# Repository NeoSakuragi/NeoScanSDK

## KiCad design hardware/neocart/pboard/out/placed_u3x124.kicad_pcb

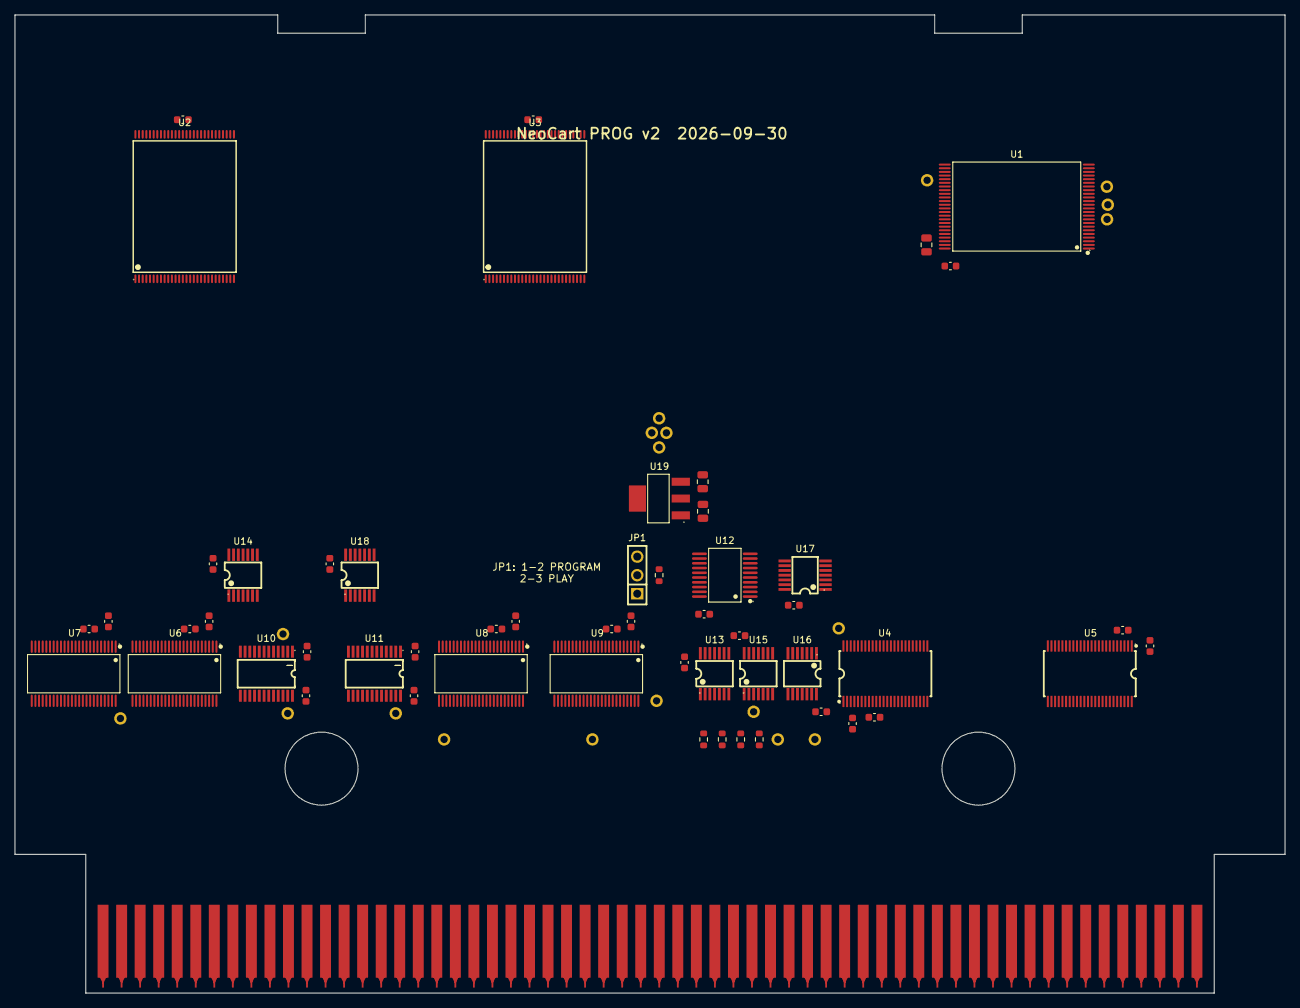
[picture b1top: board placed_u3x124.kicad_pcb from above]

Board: 2 copper layers, 174.0 x 134.0 mm, 75 parts (1 on the bottom side), 206 nets, no tracks yet.

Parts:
C1, C2, C3: 10u; C_0805_2012Metric
C4, C5, C6, C7, C8, C9, C10, C11, C12, C13, C14, C15, C16, C17, C18, C19, C20, C21, C22, C23, C24, C25, C26, C27, C28, C29: 100n; C_0603_1608Metric
J1: NeoGeo MVS Prog B Side Edge; neogeo-mvs-prog-b-side-edge
J2: NeoGeo MVS Prog A Side Edge; neogeo-mvs-prog-a-side-edge
JP1: MODE; HDR-TH_03P-P2.54-V-M
R1, R2, R3, R4, R5: 10k; R_0603_1608Metric
TP1, TP2: GND; TP_PTH_1.0
TP3: P3V3; TP_PTH_1.0
TP4: VCC5; TP_PTH_1.0
TP5: nPROG; TP_PTH_1.0
TP6: VDIR; TP_PTH_1.0
TP7: nP_OE; TP_PTH_1.0
TP8: nXCVR_EN; TP_PTH_1.0
TP9: FA19; TP_PTH_1.0
TP10: FA20; TP_PTH_1.0
TP11: FA21; TP_PTH_1.0
TP12: nVA_BUFOE; TP_PTH_1.0
TP13: nVB_BUFOE; TP_PTH_1.0
TP14: nRMPX; TP_PTH_1.0
TP15: nPMPX; TP_PTH_1.0
TP16: nAS; TP_PTH_1.0
TP17: CLK68K; TP_PTH_1.0
TP18: CLK4M; TP_PTH_1.0
TP19: nSLOTCS; TP_PTH_1.0
U1: S29GL064N; TSOP-48_L12.0-W18.4-P0.50-LS20.0-BL
U2, U3: S29GL128P; TSOP-56_L18.4-W14.0-P0.50-LS20.0-TL
U4, U5: SN74LVC16245A; TSSOP-48_L12.5-W6.1-P0.50-LS8.1-BL
U6, U7, U8, U9: 74LVC16374A; TSSOP-48_L12.6-W6.2-P0.50-LS8.1-BL
U10, U11: 74LVC8T245; TSSOP-24_L7.8-W4.4-P0.65-LS6.4-BL
U12: SN74AHC273; SSOP-20_L7.5-W5.2-P0.65-LS8.0-BL
U13, U14: SN74LVC08A; TSSOP-14_L5.0-W4.4-P0.65-LS6.4-BL
U15, U16, U17: 74LVC32A; TSSOP-14_L5.0-W4.4-P0.65-LS6.4-BL
U18: SN74LVC04A; TSSOP-14_L5.0-W4.4-P0.65-LS6.4-BL
U19: AMS1117-3.3; SOT-223-3_L6.5-W3.4-P2.30-LS7.0-BR

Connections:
A1: J1.5 (A1), U5.47
A2: J1.6 (A2), U5.46
A3: J1.7 (A3), U5.44
A4: J1.8 (A4), U5.43
A5: J1.9 (A5), U5.41
A6: J1.10 (A6), U5.40
A7: J1.11 (A7), U5.38
A8: J1.12 (A8), U5.37
A9: J1.13 (A9), U5.36
A10: J1.14 (A10), U5.35
A11: J1.15 (A11), U5.33
A12: J1.16 (A12), U5.32
A13: J1.17 (A13), U5.30
A14: J1.18 (A14), U5.29
A15: J1.19 (A15), U5.27
A16: J1.20 (A16), U5.26
A17: J1.21 (A17), U16.12
A18: J1.22 (A18), U17.1
A19: J1.23 (A19), U17.4
BANK0: U12.2, U16.1
BANK1: U12.5, U16.4
BANK2: U12.6, U16.9
CLK4M: J1.34 (4MB), TP18.1
CLK68K: J1.24 (68KCLKB), TP17.1
D0: J2.5 (D0), U4.23
D1: J2.6 (D1), U4.22
D2: J2.7 (D2), U4.20
D3: J2.8 (D3), U4.19
D4: J2.9 (D4), U4.17
D5: J2.10 (D5), U4.16
D6: J2.11 (D6), U4.14
D7: J2.12 (D7), U4.13
D8: J2.13 (D8), U4.12
D9: J2.14 (D9), U4.11
D10: J2.15 (D10), U4.9
D11: J2.16 (D11), U4.8
D12: J2.17 (D12), U4.6
D13: J2.18 (D13), U4.5
D14: J2.19 (D14), U4.3
D15: J2.20 (D15), U4.2
FA0: U1.25, U5.2
FA1: U1.24, U5.3
FA2: U1.23, U5.5
FA3: U1.22, U5.6
FA4: U1.21, U5.8
FA5: U1.20, U5.9
FA6: U1.19, U5.11
FA7: U1.18, U5.12
FA8: U1.8, U5.13
FA9: U1.7, U5.14
FA10: U1.6, U5.16
FA11: U1.5, U5.17
FA12: U1.4, U5.19
FA13: U1.3, U5.20
FA14: U1.2, U5.22
FA15: U1.1, U5.23
FA16: U1.48, U16.11
FA17: U1.17, U17.3
FA18: U1.16, U17.6
FA19: TP9.1, U1.9, U16.3
FA20: TP10.1, U1.10, U16.6
FA21: TP11.1, U1.13, U16.8
FD0: U1.29, U4.26, U12.3
FD1: U1.31, U4.27, U12.4
FD2: U1.33, U4.29, U12.7
FD3: U1.35, U4.30
FD4: U1.38, U4.32
FD5: U1.40, U4.33
FD6: U1.42, U4.35
FD7: U1.44, U4.36
FD8: U1.30, U4.37
FD9: U1.32, U4.38
FD10: U1.34, U4.40
FD11: U1.36, U4.41
FD12: U1.39, U4.43
FD13: U1.41, U4.44
FD14: U1.43, U4.46
FD15: U1.45, U4.47
GND: C1.2, C2.2, C3.2, C4.2, C5.2, C6.2, C7.2, C8.2, C9.2, C10.2, C11.2, C12.2, C13.2, C14.2, C15.2, C16.2, C17.2, C18.2, C19.2, C20.2, C21.2, C22.2, C23.2, C24.2, C25.2, C26.2, C27.2, C28.2, C29.2, J1.1 (GND), J1.2 (GND), J1.3 (GND), J1.4 (GND), J1.57 (GND), J1.58 (GND), J1.59 (GND), J1.60 (GND), J2.1 (GND), J2.2 (GND), J2.3 (GND), J2.4 (GND), J2.57 (GND), J2.58 (GND), J2.59 (GND), J2.60 (GND), JP1.2, TP1.1, TP2.1, U1.26, U1.27, U1.46, U2.32, U2.33, U2.52, U2.53, U3.32, U3.33, U3.52, U3.53, U4.4, U4.10, U4.15, U4.21, U4.28, U4.34, U4.39, U4.45, U5.4, U5.10, U5.15, U5.21, U5.25, U5.28, U5.34, U5.39, U5.45, U5.48, U6.1, U6.4, U6.10, U6.15, U6.21, U6.24, U6.26, U6.27, U6.28, U6.29, U6.30, U6.32, U6.33, U6.34, U6.39, U6.45, U7.1, U7.4, U7.10, U7.15, U7.21, U7.24, U7.26, U7.27, U7.28, U7.34, U7.39, U7.45, U8.1, U8.4, U8.10, U8.15, U8.21, U8.24, U8.26, U8.27, U8.28, U8.29, U8.30, U8.34, U8.39, U8.45, U9.1, U9.4, U9.10, U9.15, U9.21, U9.24, U9.26, U9.27, U9.28, U9.29, U9.30, U9.34, U9.39, U9.45, U10.11, U10.12, U10.13, U11.11, U11.12, U11.13, U12.8, U12.10, U12.13, U12.14, U12.17, U12.18, U13.7, U14.7, U15.7, U16.7, U16.13, U17.2, U17.5, U17.7, U17.9, U17.10, U17.12, U17.13, U18.5, U18.7, U18.9, U18.11, U18.13, U19.1
P3V3: C2.1, C3.1, C4.1, C5.1, C6.1, C7.1, C8.1, C9.1, C10.1, C11.1, C12.1, C13.1, C14.1, C15.1, C16.1, C17.1, C18.1, C19.1, C20.1, C21.1, C22.1, C23.1, C24.1, C25.1, C26.1, C28.1, R1.2, TP3.1, U1.12, U1.14, U1.37, U1.47, U2.14, U2.16, U2.29, U2.43, U3.14, U3.16, U3.29, U3.43, U4.7, U4.18, U4.31, U4.42, U5.1, U5.7, U5.18, U5.24, U5.31, U5.42, U6.7, U6.18, U6.31, U6.42, U7.7, U7.18, U7.31, U7.42, U8.7, U8.18, U8.31, U8.42, U9.7, U9.18, U9.31, U9.42, U10.1, U11.1, U12.20, U13.14, U14.14, U15.14, U16.14, U17.14, U18.14, U19.2, U19.4
RW: J2.21 (R/W), U4.1, U4.24, U15.12
SDPA8: J2.43 (SDPA8), U8.36, U9.36
SDPA9: J2.44 (SDPA9), U8.35, U9.35
SDPA10: J2.45 (SDPA10), U8.33, U9.33
SDPA11: J2.46 (SDPA11), U8.32, U9.32
SDPAD0: J1.41 (SDPAD0), U8.47, U9.47, U11.21
SDPAD1: J1.42 (SDPAD1), U8.46, U9.46, U11.20
SDPAD2: J1.43 (SDPAD2), U8.44, U9.44, U11.19
SDPAD3: J1.44 (SDPAD3), U8.43, U9.43, U11.18
SDPAD4: J1.45 (SDPAD4), U8.41, U9.41, U11.17
SDPAD5: J1.46 (SDPAD5), U8.40, U9.40, U11.16
SDPAD6: J1.47 (SDPAD6), U8.38, U9.38, U11.15
SDPAD7: J1.48 (SDPAD7), U8.37, U9.37, U11.14
SDPMPX: J2.47 (SDPMPX), U8.25, U8.48, U18.3
SDRA8: J2.49 (SDRA8), U6.36, U7.36
SDRA9: J2.50 (SDRA9), U6.35, U7.35
SDRA20: J2.51 (SDRA20), U7.33
SDRA21: J2.52 (SDRA21), U7.32
SDRA22: J2.53 (SDRA22), U7.30
SDRA23: J2.54 (SDRA23), U7.29
SDRAD0: J1.49 (SDRAD0), U6.47, U7.47, U10.21
SDRAD1: J1.50 (SDRAD1), U6.46, U7.46, U10.20
SDRAD2: J1.51 (SDRAD2), U6.44, U7.44, U10.19
SDRAD3: J1.52 (SDRAD3), U6.43, U7.43, U10.18
SDRAD4: J1.53 (SDRAD4), U6.41, U7.41, U10.17
SDRAD5: J1.54 (SDRAD5), U6.40, U7.40, U10.16
SDRAD6: J1.55 (SDRAD6), U6.38, U7.38, U10.15
SDRAD7: J1.56 (SDRAD7), U6.37, U7.37, U10.14
SDRMPX: J2.55 (SDRMPX), U6.25, U6.48, U18.1
VA_ADR0: U2.51, U6.2
VA_ADR1: U2.31, U6.3
VA_ADR2: U2.26, U6.5
VA_ADR3: U2.25, U6.6
VA_ADR4: U2.24, U6.8
VA_ADR5: U2.23, U6.9
VA_ADR6: U2.22, U6.11
VA_ADR7: U2.21, U6.12
VA_ADR8: U2.20, U6.13
VA_ADR9: U2.10, U6.14
VA_ADR10: U2.9, U7.2
VA_ADR11: U2.8, U7.3
VA_ADR12: U2.7, U7.5
VA_ADR13: U2.6, U7.6
VA_ADR14: U2.5, U7.8
VA_ADR15: U2.4, U7.9
VA_ADR16: U2.3, U7.11
VA_ADR17: U2.54, U7.12
VA_ADR18: U2.19, U7.13
VA_ADR19: U2.18, U7.14
VA_ADR20: U2.11, U7.16
VA_ADR21: U2.12, U7.17
VA_ADR22: U2.15, U7.19
VA_ADR23: U2.2, U7.20
VA_DQ0: U2.35, U10.3
VA_DQ1: U2.37, U10.4
VA_DQ2: U2.39, U10.5
VA_DQ3: U2.41, U10.6
VA_DQ4: U2.44, U10.7
VA_DQ5: U2.46, U10.8
VA_DQ6: U2.48, U10.9
VA_DQ7: U2.50, U10.10
VB_ADR0: U3.51, U8.2
VB_ADR1: U3.31, U8.3
VB_ADR2: U3.26, U8.5
VB_ADR3: U3.25, U8.6
VB_ADR4: U3.24, U8.8
VB_ADR5: U3.23, U8.9
VB_ADR6: U3.22, U8.11
VB_ADR7: U3.21, U8.12
VB_ADR8: U3.20, U8.13
VB_ADR9: U3.10, U8.14
VB_ADR10: U3.9, U8.16
VB_ADR11: U3.8, U8.17
VB_ADR12: U3.7, U9.2
VB_ADR13: U3.6, U9.3
VB_ADR14: U3.5, U9.5
VB_ADR15: U3.4, U9.6
VB_ADR16: U3.3, U9.8
VB_ADR17: U3.54, U9.9
VB_ADR18: U3.19, U9.11
VB_ADR19: U3.18, U9.12
VB_ADR20: U3.11, U9.13
VB_ADR21: U3.12, U9.14
VB_ADR22: U3.15, U9.16
VB_ADR23: U3.2, U9.17
VB_DQ0: U3.35, U11.3
VB_DQ1: U3.37, U11.4
VB_DQ2: U3.39, U11.5
VB_DQ3: U3.41, U11.6
VB_DQ4: U3.44, U11.7
VB_DQ5: U3.46, U11.8
VB_DQ6: U3.48, U11.9
VB_DQ7: U3.50, U11.10
VCC5: C1.1, C27.1, C29.1, J1.29 (VCC), J1.30 (VCC), J1.31 (VCC), J1.32 (VCC), J2.29 (VCC), J2.30 (VCC), J2.31 (VCC), J2.32 (VCC), R2.2, R3.2, R4.2, R5.2, TP4.1, U10.23, U10.24, U11.23, U11.24, U19.3
VDIR: TP6.1, U10.2, U11.2, U15.11
nAS: J2.22 (AS), TP16.1
nPDTACK: J1.28 (PDTACK), R5.1
nPMPX: TP15.1, U9.25, U9.48, U18.4
nPORTADRS: J2.33 (PORTADRS), U16.2, U16.5, U16.10
nPORTOE: U13.3, U13.5
nPORTOEL: J2.26 (PORTOEL), U13.1
nPORTOEU: J2.25 (PORTOEU), U13.2
nPORTWEL: J2.28 (PORTWEL), U12.11, U13.10
nPORTWEU: J2.27 (PORTWEU), U15.1
nPROG: JP1.1, R1.1, TP5.1, U15.2, U15.5, U15.10, U15.13
nPWAIT0: J1.26 (PWAIT0), R3.1
nPWAIT1: J1.27 (PWAIT1), R4.1
nP_OE: TP7.1, U1.28, U13.6, U13.9
nP_WE: U1.11, U13.13, U15.3
nRESET: J1.35 (RESET), U12.1
nRMPX: TP14.1, U7.25, U7.48, U18.2
nROMOE: J1.33 (ROMOE), U13.4
nROMOEL: J2.24 (ROMOEL), U15.9
nROMOEU: J2.23 (ROMOEU), U15.4
nROMWAIT: J1.25 (ROMWAIT), R2.1
nSDPOE: J2.48 (SDPOE), U14.4, U14.5
nSDROE: J2.56 (SDROE), U14.1, U14.2
nSLOTCS: J2.42 (SLOTCS), TP19.1
nVA_BUFOE: TP12.1, U10.22, U14.8
nVA_OE: U2.34, U14.3, U14.9
nVA_WE: U2.13, U14.10, U15.6
nVB_BUFOE: TP13.1, U11.22, U14.11
nVB_OE: U3.34, U14.6, U14.12
nVB_WE: U3.13, U14.13, U15.8
nXCVR_EN: TP8.1, U4.25, U4.48, U13.11
nXEN1: U13.8, U13.12

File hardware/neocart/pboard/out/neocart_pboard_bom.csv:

Comment,Designator,Footprint,LCSC Part #
100n,"C23,C5,C17,C15,C16,C26,C19,C22,C27,C8,C14,C21,C18,C28,C6,C4,C12,C9,C25,C7,C11,C20,C10,C24,C13",C0603,C14663
74LVC16245A,"U5,U4",TSSOP-48_L12.5-W6.1-P0.50-LS8.1-BL,C548160
74LVC8T245,"U11,U10",TSSOP-24_L7.8-W4.4-P0.65-LS6.4-BL,C458788
10k,"R3,R1,R5,R2,R4",R0603,C25804
74LVC08A,"U13,U14",TSSOP-14_L5.0-W4.4-P0.65-LS6.4-BL,C6053
74LVC32A,"U17,U16,U15",TSSOP-14_L5.0-W4.4-P0.65-LS6.4-BL,C6087
74LVC16374A,"U9,U8,U7,U6",TSSOP-48_L12.6-W6.2-P0.50-LS8.1-BL,C6074
10u,"C2,C3,C1",C0805,C15850
SN74AHC273,U12,SSOP-20_L7.5-W5.2-P0.65-LS8.0-BL,C2877489
S29GL064N,U1,TSOP-48_L12.0-W18.4-P0.50-LS20.0-BL,C117907
S29GL128P,U2,TSOP-56_L18.4-W14.0-P0.50-LS20.0-TL,C914939
SN74LVC04A,U18,TSSOP-14_L5.0-W4.4-P0.65-LS6.4-BL,C352968
AMS1117-3.3,U19,SOT-223-3_L6.5-W3.4-P2.30-LS7.0-BR,C6186
